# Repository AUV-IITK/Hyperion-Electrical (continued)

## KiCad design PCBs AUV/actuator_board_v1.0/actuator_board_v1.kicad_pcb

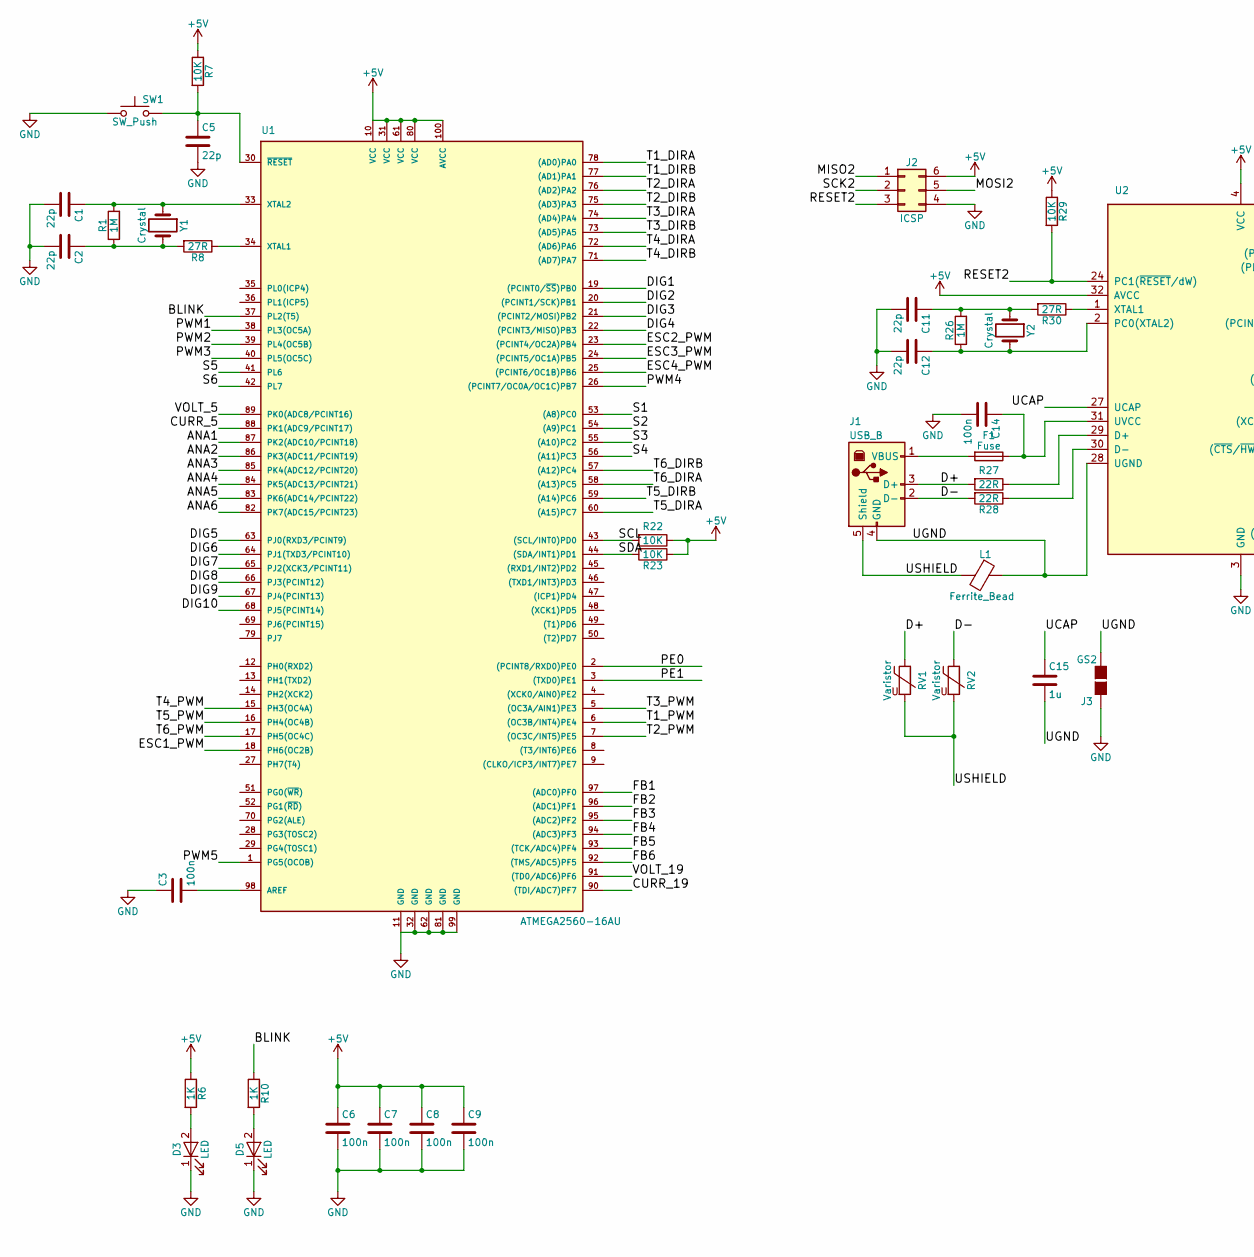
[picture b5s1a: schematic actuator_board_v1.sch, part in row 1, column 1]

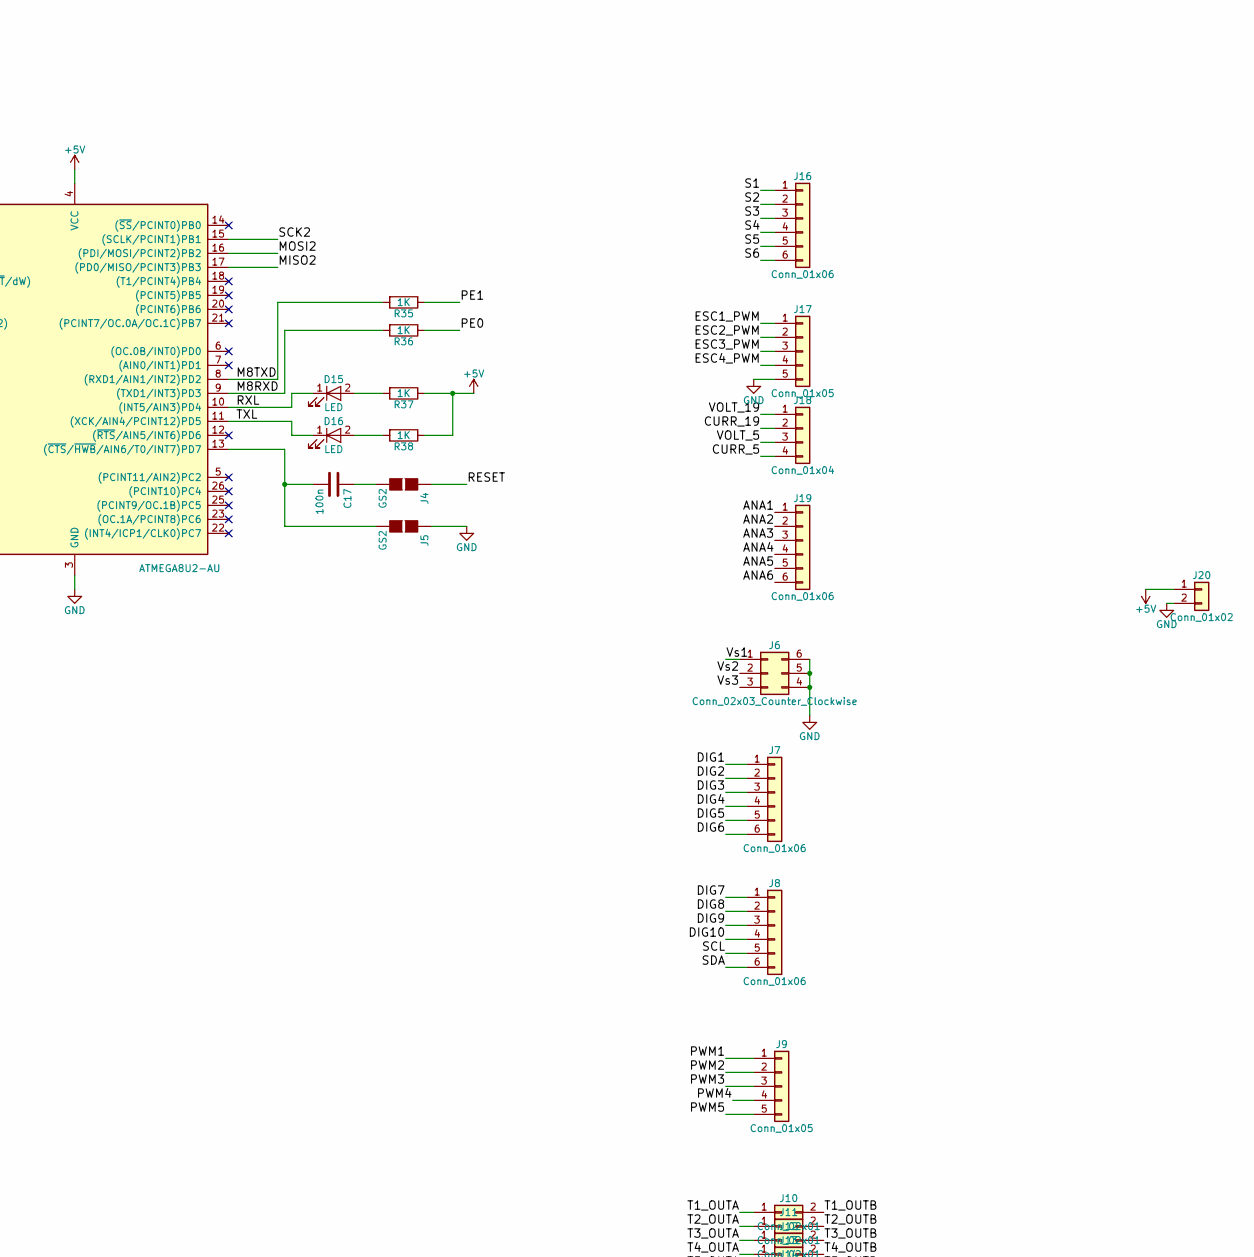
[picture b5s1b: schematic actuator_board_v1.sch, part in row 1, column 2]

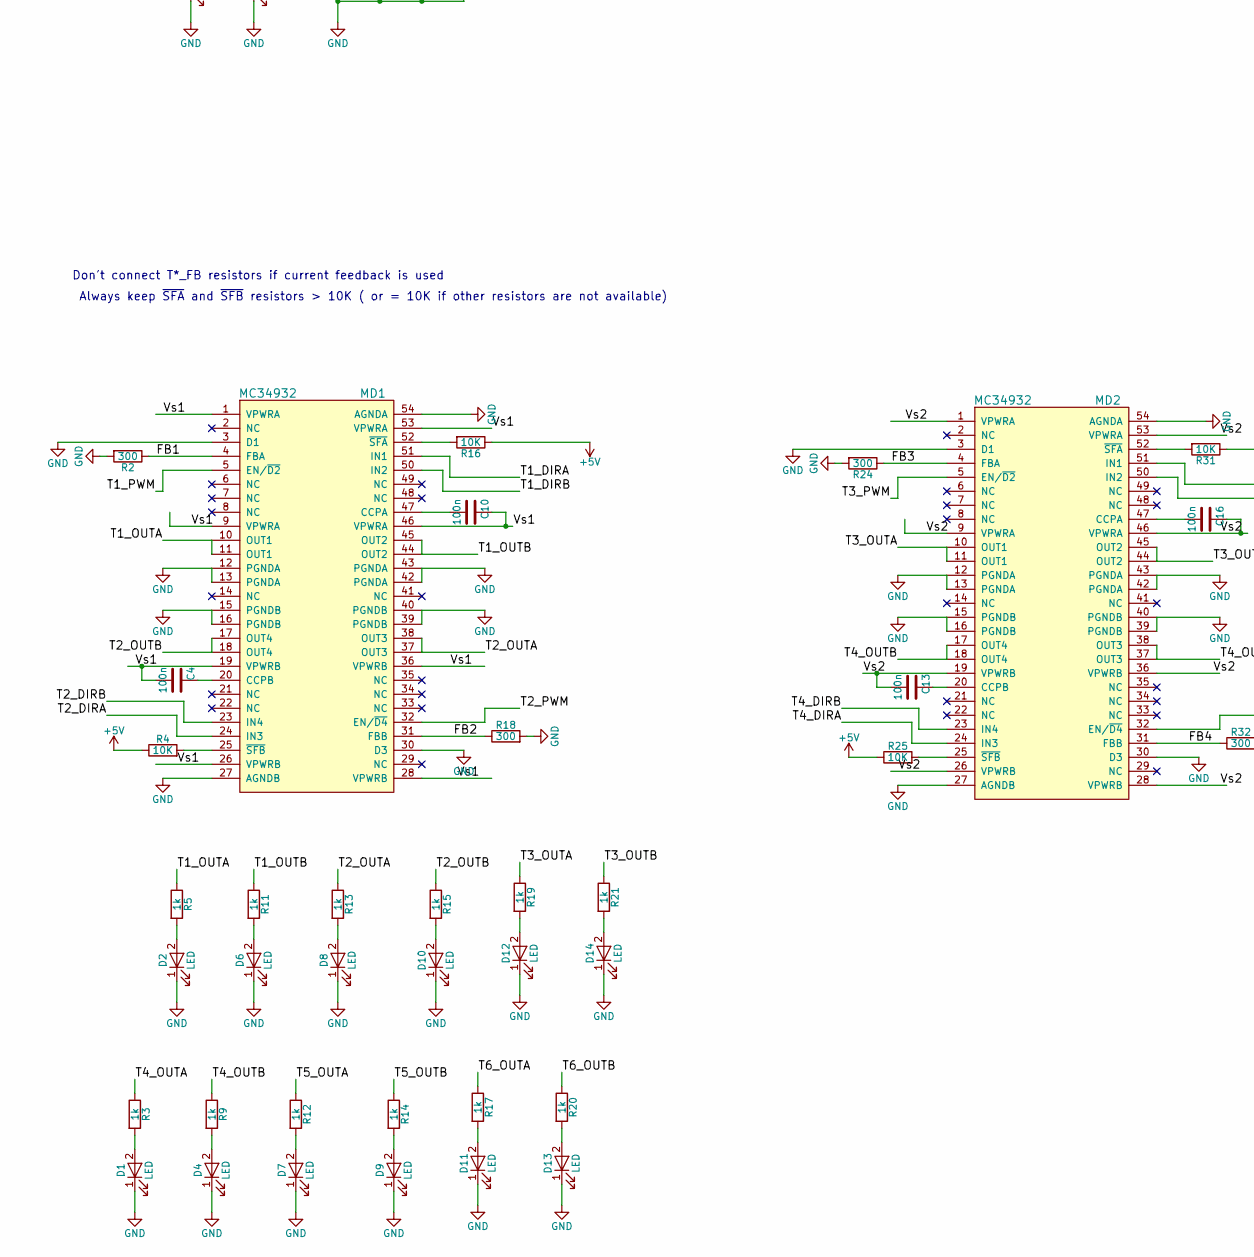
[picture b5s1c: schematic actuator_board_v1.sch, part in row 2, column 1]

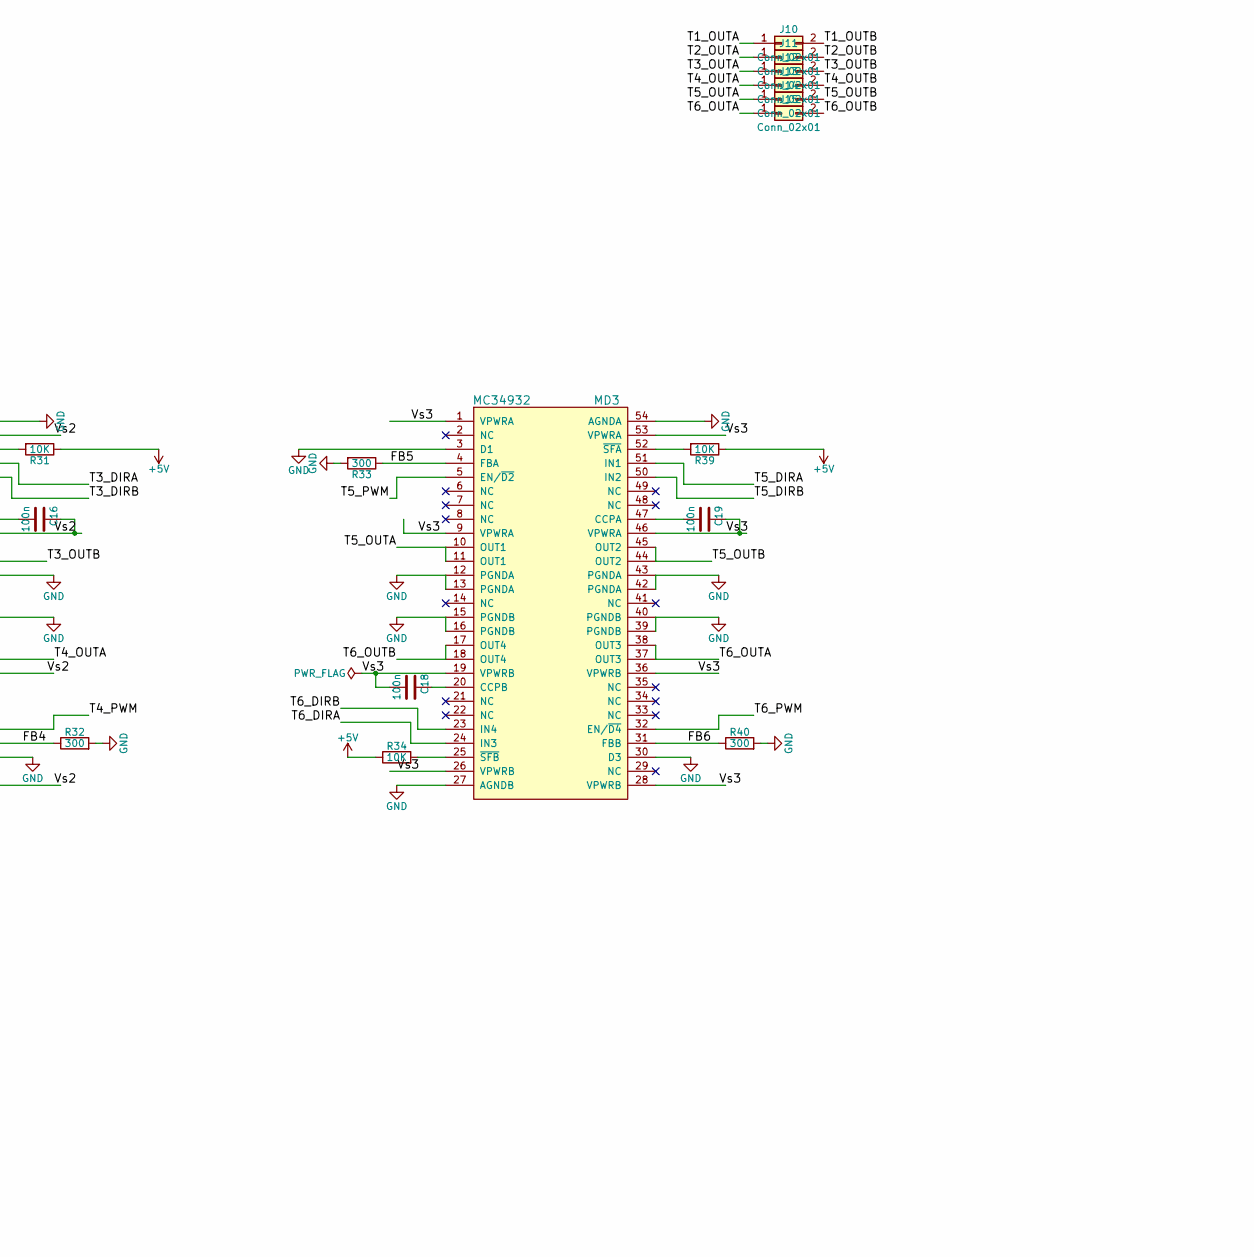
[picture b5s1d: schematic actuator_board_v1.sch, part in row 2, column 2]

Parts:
C1, C2, C5, C11, C12: 22p; C_1206
C3, C4, C6, C7, C8, C9, C10, C13, C14, C16, C17, C18, C19: 100n; C_1206
C15: 1u; C_1206
D1, D2, D3, D4, D5, D6, D7, D8, D9, D10, D11, D12, D13, D14, D15, D16: LED; LED_1206
F1: Fuse
J1: USB_B
J2: ICSP
J3, J4, J5: GS2
J6: Conn_02x03_Counter_Clockwise; Molex_MegaFit_2x03x5.70mm_Straight
J7, J8, J16, J19: Conn_01x06; Molex_PicoClasp_501331-0607_1x06_P1.0mm_Vertical
J9, J17: Conn_01x05; Molex_PicoClasp_501331-0507_1x05_P1.0mm_Vertical
J10, J11, J12, J13, J14, J15: Conn_02x01; Molex_MegaFit_2x01x5.70mm_Straight
J18: Conn_01x04; Molex_PicoClasp_501331-0407_1x04_P1.0mm_Vertical
J20: Conn_01x02; Molex_MegaFit_2x01x5.70mm_Straight
L1: Ferrite_Bead; 0603-NO
MD1, MD2, MD3: MC34932; SOIC-54(SOICW-EP-54)
R1, R26: 1M; R_1206
R2, R18, R24, R32, R33, R40: 300; R_1206
R3, R5, R9, R11, R12, R13, R14, R15, R17, R19, R20, R21: 1k; R_1206
R4, R7, R16, R22, R23, R25, R29, R31, R34, R39: 10K; R_1206
R6, R10, R35, R36, R37, R38: 1K; R_1206
R8, R30: 27R; R_1206
R27, R28: 22R; R_1206
RV1, RV2: Varistor; 0603-NO
SW1: SW_Push; SW_PUSH_6mm_h5mm
U1: ATMEGA2560-16AU; TQFP100
U2: ATMEGA8U2-AU; TQFP-32
Y1, Y2: Crystal; Crystal_SMD_0603-4pin_6.0x3.5mm

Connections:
+5V: C6.1, C7.1, C8.1, C9.1, J2.6, J20.1, R4.1, R6.1, R7.1, R16.1, R22.1, R23.1, R25.1, R29.1, R31.1, R34.1, R37.1, R38.1, R39.1, U1.10 (VCC), U1.31 (VCC), U1.61 (VCC), U1.80 (VCC), U1.100 (AVCC), U2.4 (VCC), U2.32 (AVCC)
/ANA1: J19.1, U1.87 (PK2(ADC10/PCINT18))
/ANA2: J19.2, U1.86 (PK3(ADC11/PCINT19))
/ANA3: J19.3, U1.85 (PK4(ADC12/PCINT20))
/ANA4: J19.4, U1.84 (PK5(ADC13/PCINT21))
/ANA5: J19.5, U1.83 (PK6(ADC14/PCINT22))
/ANA6: J19.6, U1.82 (PK7(ADC15/PCINT23))
/BLINK: R10.1, U1.37 (PL2(T5))
/CURR_5: J18.4, U1.88 (PK1(ADC9/PCINT17))
/CURR_19: J18.2, U1.90 ((TDI/ADC7)PF7)
/D+: J1.3 (D+), R27.2, RV1.1
/D-: J1.2 (D-), R28.2, RV2.1
/DIG1: J7.1, U1.19 ((PCINT0/~SS~)PB0)
/DIG2: J7.2, U1.20 ((PCINT1/SCK)PB1)
/DIG3: J7.3, U1.21 ((PCINT2/MOSI)PB2)
/DIG4: J7.4, U1.22 ((PCINT3/MISO)PB3)
/DIG5: J7.5, U1.63 (PJ0(RXD3/PCINT9))
/DIG6: J7.6, U1.64 (PJ1(TXD3/PCINT10))
/DIG7: J8.1, U1.65 (PJ2(XCK3/PCINT11))
/DIG8: J8.2, U1.66 (PJ3(PCINT12))
/DIG9: J8.3, U1.67 (PJ4(PCINT13))
/DIG10: J8.4, U1.68 (PJ5(PCINT14))
/ESC1_PWM: J17.1, U1.18 (PH6(OC2B))
/ESC2_PWM: J17.2, U1.23 ((PCINT4/OC2A)PB4)
/ESC3_PWM: J17.3, U1.24 ((PCINT5/OC1A)PB5)
/ESC4_PWM: J17.4, U1.25 ((PCINT6/OC1B)PB6)
/FB1: MD1.4 (FBA), R2.1, U1.97 ((ADC0)PF0)
/FB2: MD1.31 (FBB), R18.1, U1.96 ((ADC1)PF1)
/FB3: MD2.4 (FBA), R24.1, U1.95 ((ADC2)PF2)
/FB4: MD2.31 (FBB), R32.1, U1.94 ((ADC3)PF3)
/FB5: MD3.4 (FBA), R33.1, U1.93 ((TCK/ADC4)PF4)
/FB6: MD3.31 (FBB), R40.1, U1.92 ((TMS/ADC5)PF5)
/M8RXD: R36.2, U2.9 ((TXD1/INT3)PD3)
/M8TXD: R35.2, U2.8 ((RXD1/AIN1/INT2)PD2)
/MISO2: J2.1, U2.17 ((PD0/MISO/PCINT3)PB3)
/MOSI2: J2.5, U2.16 ((PDI/MOSI/PCINT2)PB2)
/PE0: R36.1, U1.2 ((PCINT8/RXD0)PE0)
/PE1: R35.1, U1.3 ((TXD0)PE1)
/PWM1: J9.1, U1.38 (PL3(OC5A))
/PWM2: J9.2, U1.39 (PL4(OC5B))
/PWM3: J9.3, U1.40 (PL5(OC5C))
/PWM4: J9.4, U1.26 ((PCINT7/OC0A/OC1C)PB7)
/PWM5: J9.5, U1.1 (PG5(OCOB))
/RESET: J4.1 (G1)
/RESET2: J2.3, R29.2, U2.24 (PC1(~RESET~/dW))
/RXL: D15.1 (K), U2.10 ((INT5/AIN3)PD4)
/S1: J16.1, U1.53 ((A8)PC0)
/S2: J16.2, U1.54 ((A9)PC1)
/S3: J16.3, U1.55 ((A10)PC2)
/S4: J16.4, U1.56 ((A11)PC3)
/S5: J16.5, U1.41 (PL6)
/S6: J16.6, U1.42 (PL7)
/SCK2: J2.2, U2.15 ((SCLK/PCINT1)PB1)
/SCL: J8.5, R22.2, U1.43 ((SCL/INT0)PD0)
/SDA: J8.6, R23.2, U1.44 ((SDA/INT1)PD1)
/T1_DIRA: MD1.51 (IN1), U1.78 ((AD0)PA0)
/T1_DIRB: MD1.50 (IN2), U1.77 ((AD1)PA1)
/T1_OUTA: J10.1, MD1.10 (OUT1), MD1.11 (OUT1), R5.1
/T1_OUTB: J10.2, MD1.44 (OUT2), MD1.45 (OUT2), R11.1
/T1_PWM: MD1.5 (EN/~D2~), U1.6 ((OC3B/INT4)PE4)
/T2_DIRA: MD1.24 (IN3), U1.76 ((AD2)PA2)
/T2_DIRB: MD1.23 (IN4), U1.75 ((AD3)PA3)
/T2_OUTA: J11.1, MD1.37 (OUT3), MD1.38 (OUT3), R13.1
/T2_OUTB: J11.2, MD1.17 (OUT4), MD1.18 (OUT4), R15.1
/T2_PWM: MD1.32 (EN/~D4~), U1.7 ((OC3C/INT5)PE5)
/T3_DIRA: MD2.51 (IN1), U1.74 ((AD4)PA4)
/T3_DIRB: MD2.50 (IN2), U1.73 ((AD5)PA5)
/T3_OUTA: J12.1, MD2.10 (OUT1), MD2.11 (OUT1), R19.1
/T3_OUTB: J12.2, MD2.44 (OUT2), MD2.45 (OUT2), R21.1
/T3_PWM: MD2.5 (EN/~D2~), U1.5 ((OC3A/AIN1)PE3)
/T4_DIRA: MD2.24 (IN3), U1.72 ((AD6)PA6)
/T4_DIRB: MD2.23 (IN4), U1.71 ((AD7)PA7)
/T4_OUTA: J13.1, MD2.37 (OUT3), MD2.38 (OUT3), R3.1
/T4_OUTB: J13.2, MD2.17 (OUT4), MD2.18 (OUT4), R9.1
/T4_PWM: MD2.32 (EN/~D4~), U1.15 (PH3(OC4A))
/T5_DIRA: MD3.51 (IN1), U1.60 ((A15)PC7)
/T5_DIRB: MD3.50 (IN2), U1.59 ((A14)PC6)
/T5_OUTA: J14.1, MD3.10 (OUT1), MD3.11 (OUT1), R12.1
/T5_OUTB: J14.2, MD3.44 (OUT2), MD3.45 (OUT2), R14.1
/T5_PWM: MD3.5 (EN/~D2~), U1.16 (PH4(OC4B))
/T6_DIRA: MD3.24 (IN3), U1.58 ((A13)PC5)
/T6_DIRB: MD3.23 (IN4), U1.57 ((A12)PC4)
/T6_OUTA: J15.1, MD3.37 (OUT3), MD3.38 (OUT3), R17.1
/T6_OUTB: J15.2, MD3.17 (OUT4), MD3.18 (OUT4), R20.1
/T6_PWM: MD3.32 (EN/~D4~), U1.17 (PH5(OC4C))
/TXL: D16.1 (K), U2.11 ((XCK/AIN4/PCINT12)PD5)
/UCAP: C15.1, U2.27 (UCAP)
/UGND: C15.2, J1.4 (GND), J3.2 (G2), L1.1, U2.28 (UGND)
/USHIELD: J1.5 (Shield), L1.2, RV1.2, RV2.2
/VOLT_5: J18.3, U1.89 (PK0(ADC8/PCINT16))
/VOLT_19: J18.1, U1.91 ((TD0/ADC6)PF6)
/Vs1: C4.2, C10.1, J6.1, MD1.1 (VPWRA), MD1.9 (VPWRA), MD1.19 (VPWRB), MD1.26 (VPWRB), MD1.28 (VPWRB), MD1.36 (VPWRB), MD1.46 (VPWRA), MD1.53 (VPWRA)
/Vs2: C13.2, C16.1, J6.2, MD2.1 (VPWRA), MD2.9 (VPWRA), MD2.19 (VPWRB), MD2.26 (VPWRB), MD2.28 (VPWRB), MD2.36 (VPWRB), MD2.46 (VPWRA), MD2.53 (VPWRA)
/Vs3: C18.2, C19.1, J6.3, MD3.1 (VPWRA), MD3.9 (VPWRA), MD3.19 (VPWRB), MD3.26 (VPWRB), MD3.28 (VPWRB), MD3.36 (VPWRB), MD3.46 (VPWRA), MD3.53 (VPWRA)
GND: C1.2, C2.2, C3.1, C5.2, C6.2, C7.2, C8.2, C9.2, C11.2, C12.2, C14.2, D1.1 (K), D2.1 (K), D3.1 (K), D4.1 (K), D5.1 (K), D6.1 (K), D7.1 (K), D8.1 (K), D9.1 (K), D10.1 (K), D11.1 (K), D12.1 (K), D13.1 (K), D14.1 (K), J2.4, J3.1 (G1), J5.1 (G1), J6.4, J6.5, J6.6, J17.5, J20.2, MD1.3 (D1), MD1.12 (PGNDA), MD1.13 (PGNDA), MD1.15 (PGNDB), MD1.16 (PGNDB), MD1.27 (AGNDB), MD1.30 (D3), MD1.39 (PGNDB), MD1.40 (PGNDB), MD1.42 (PGNDA), MD1.43 (PGNDA), MD1.54 (AGNDA), MD2.3 (D1), MD2.12 (PGNDA), MD2.13 (PGNDA), MD2.15 (PGNDB), MD2.16 (PGNDB), MD2.27 (AGNDB), MD2.30 (D3), MD2.39 (PGNDB), MD2.40 (PGNDB), MD2.42 (PGNDA), MD2.43 (PGNDA), MD2.54 (AGNDA), MD3.3 (D1), MD3.12 (PGNDA), MD3.13 (PGNDA), MD3.15 (PGNDB), MD3.16 (PGNDB), MD3.27 (AGNDB), MD3.30 (D3), MD3.39 (PGNDB), MD3.40 (PGNDB), MD3.42 (PGNDA), MD3.43 (PGNDA), MD3.54 (AGNDA), R2.2, R18.2, R24.2, R32.2, R33.2, R40.2, SW1.1, U1.11 (GND), U1.32 (GND), U1.62 (GND), U1.81 (GND), U1.99 (GND), U2.3 (GND)
unnamed: C1.1, R1.2, U1.33 (XTAL2), Y1.1
unnamed: C2.1, R1.1, R8.2, Y1.2
unnamed: C3.2, U1.98 (AREF)
unnamed: C4.1, MD1.20 (CCPB)
unnamed: C5.1, R7.2, SW1.2, U1.30 (~RESET)
unnamed: C10.2, MD1.47 (CCPA)
unnamed: C11.1, R26.2, R30.2, Y2.1
unnamed: C12.1, R26.1, U2.2 (PC0(XTAL2)), Y2.2
unnamed: C13.1, MD2.20 (CCPB)
unnamed: C14.1, F1.1, U2.31 (UVCC)
unnamed: C16.2, MD2.47 (CCPA)
unnamed: C17.1, J4.2 (G2)
unnamed: C17.2, J5.2 (G2), U2.13 ((~CTS~/~HWB~/AIN6/T0/INT7)PD7)
unnamed: C18.1, MD3.20 (CCPB)
unnamed: C19.2, MD3.47 (CCPA)
unnamed: D1.2 (A), R3.2
unnamed: D2.2 (A), R5.2
unnamed: D3.2 (A), R6.2
unnamed: D4.2 (A), R9.2
unnamed: D5.2 (A), R10.2
unnamed: D6.2 (A), R11.2
unnamed: D7.2 (A), R12.2
unnamed: D8.2 (A), R13.2
unnamed: D9.2 (A), R14.2
unnamed: D10.2 (A), R15.2
unnamed: D11.2 (A), R17.2
unnamed: D12.2 (A), R19.2
unnamed: D13.2 (A), R20.2
unnamed: D14.2 (A), R21.2
unnamed: D15.2 (A), R37.2
unnamed: D16.2 (A), R38.2
unnamed: F1.2, J1.1 (VBUS)
unnamed: MD1.25 (~SFB~), R4.2
unnamed: MD1.52 (~SFA~), R16.2
unnamed: MD2.25 (~SFB~), R25.2
unnamed: MD2.52 (~SFA~), R31.2
unnamed: MD3.25 (~SFB~), R34.2
unnamed: MD3.52 (~SFA~), R39.2
unnamed: R8.1, U1.34 (XTAL1)
unnamed: R27.1, U2.29 (D+)
unnamed: R28.1, U2.30 (D-)
unnamed: R30.1, U2.1 (XTAL1)

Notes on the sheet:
Don't connect T*_FB resistors if current feedback is used
Always keep ~SFA~ and ~SFB~ resistors > 10K ( or = 10K if other resistors are not available)

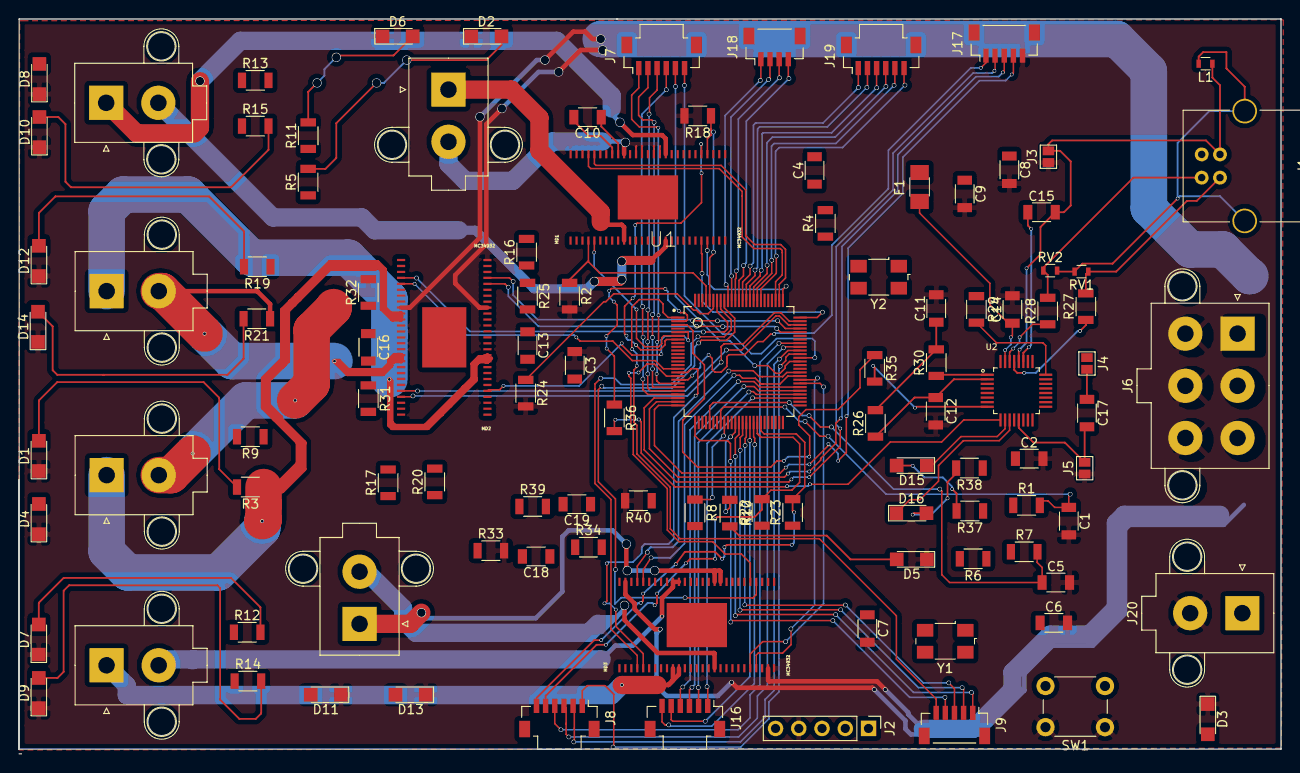
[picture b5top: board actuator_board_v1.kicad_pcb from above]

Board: 2 copper layers, 137.9 x 80.3 mm, 107 parts (0 on the bottom side), 136 nets.

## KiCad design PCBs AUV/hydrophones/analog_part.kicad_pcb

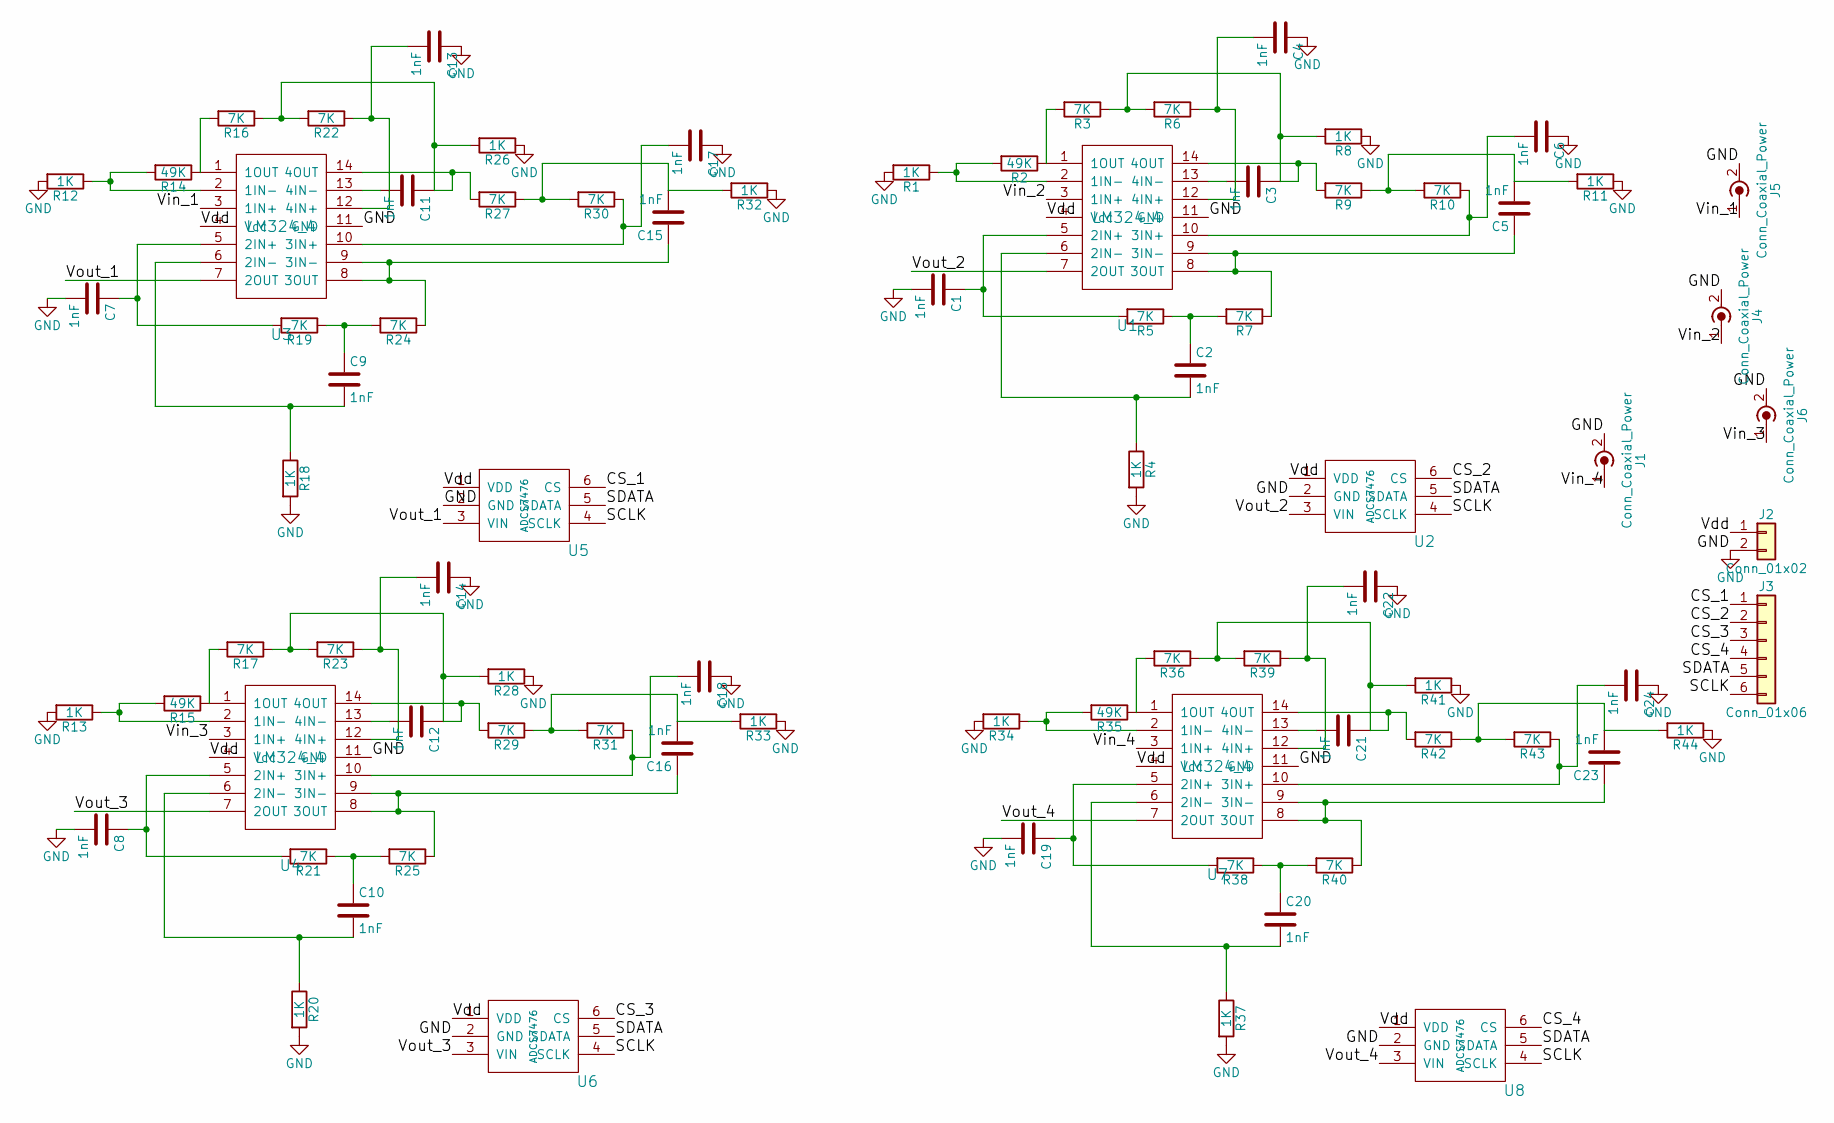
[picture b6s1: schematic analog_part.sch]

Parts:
C1, C2, C3, C4, C5, C6, C7, C8, C9, C10, C11, C12, C13, C14, C15, C16, C17, C18, C19, C20, C21, C22, C23, C24: 1nF; C_1206_HandSoldering
J1, J4, J5, J6: Conn_Coaxial_Power; bnc-ci
J2: Conn_01x02; Pin_Header_Angled_1x02_Pitch2.54mm
J3: Conn_01x06; Pin_Header_Angled_1x06_Pitch2.54mm
R1, R4, R8, R11, R12, R13, R18, R20, R26, R28, R32, R33, R34, R37, R41, R44: 1K; R_1206_HandSoldering
R2, R14, R15, R35: 49K; R_1206_HandSoldering
R3, R5, R6, R7, R9, R10, R16, R17, R19, R21, R22, R23, R24, R25, R27, R29, R30, R31, R36, R38, R39, R40, R42, R43: 7K; R_1206_HandSoldering
U1, U3, U4, U7: LM324_4; TSSOP-14_4.4x5mm_Pitch0.65mm
U2, U5, U6, U8: ADCS7476; SOT-23-6_Handsoldering

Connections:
/CS_1: J3.1, U5.6 (CS)
/CS_2: J3.2, U2.6 (CS)
/CS_3: J3.3, U6.6 (CS)
/CS_4: J3.4, U8.6 (CS)
/SCLK: J3.6, U2.4 (SCLK), U5.4 (SCLK), U6.4 (SCLK), U8.4 (SCLK)
/SDATA: J3.5, U2.5 (SDATA), U5.5 (SDATA), U6.5 (SDATA), U8.5 (SDATA)
/Vdd: J2.1, U1.4 (Vcc), U2.1 (VDD), U3.4 (Vcc), U4.4 (Vcc), U5.1 (VDD), U6.1 (VDD), U7.4 (Vcc), U8.1 (VDD)
/Vin_1: J5.1 (In), U3.3 (1IN+)
/Vin_2: J4.1 (In), U1.3 (1IN+)
/Vin_3: J6.1 (In), U4.3 (1IN+)
/Vin_4: J1.1 (In), U7.3 (1IN+)
/Vout_1: U3.7 (2OUT), U5.3 (VIN)
/Vout_2: U1.7 (2OUT), U2.3 (VIN)
/Vout_3: U4.7 (2OUT), U6.3 (VIN)
/Vout_4: U7.7 (2OUT), U8.3 (VIN)
GND: C1.2, C4.1, C6.1, C7.2, C8.2, C13.1, C14.1, C17.1, C18.1, C19.2, C22.1, C24.1, J1.2 (Ext), J2.2, J4.2 (Ext), J5.2 (Ext), J6.2 (Ext), R1.2, R4.2, R8.1, R11.1, R12.2, R13.2, R18.2, R20.2, R26.1, R28.1, R32.1, R33.1, R34.2, R37.2, R41.1, R44.1, U1.11 (GND), U2.2 (GND), U3.11 (GND), U4.11 (GND), U5.2 (GND), U6.2 (GND), U7.11 (GND), U8.2 (GND)
unnamed: C1.1, R5.2, U1.5 (2IN+)
unnamed: C2.1, R5.1, R7.2
unnamed: C2.2, R4.1, U1.6 (2IN-)
unnamed: C3.1, R3.1, R6.2, R8.2, R9.2, U1.14 (4OUT)
unnamed: C3.2, U1.13 (4IN-)
unnamed: C4.2, R6.1, U1.12 (4IN+)
unnamed: C5.1, R7.1, U1.8 (3OUT), U1.9 (3IN-)
unnamed: C5.2, R9.1, R10.2, R11.2
unnamed: C6.2, R10.1, U1.10 (3IN+)
unnamed: C7.1, R19.2, U3.5 (2IN+)
unnamed: C8.1, R21.2, U4.5 (2IN+)
unnamed: C9.1, R19.1, R24.2
unnamed: C9.2, R18.1, U3.6 (2IN-)
unnamed: C10.1, R21.1, R25.2
unnamed: C10.2, R20.1, U4.6 (2IN-)
unnamed: C11.1, R16.1, R22.2, R26.2, R27.2, U3.14 (4OUT)
unnamed: C11.2, U3.13 (4IN-)
unnamed: C12.1, R17.1, R23.2, R28.2, R29.2, U4.14 (4OUT)
unnamed: C12.2, U4.13 (4IN-)
unnamed: C13.2, R22.1, U3.12 (4IN+)
unnamed: C14.2, R23.1, U4.12 (4IN+)
unnamed: C15.1, R24.1, U3.8 (3OUT), U3.9 (3IN-)
unnamed: C15.2, R27.1, R30.2, R32.2
unnamed: C16.1, R25.1, U4.8 (3OUT), U4.9 (3IN-)
unnamed: C16.2, R29.1, R31.2, R33.2
unnamed: C17.2, R30.1, U3.10 (3IN+)
unnamed: C18.2, R31.1, U4.10 (3IN+)
unnamed: C19.1, R38.2, U7.5 (2IN+)
unnamed: C20.1, R38.1, R40.2
unnamed: C20.2, R37.1, U7.6 (2IN-)
unnamed: C21.1, R36.1, R39.2, R41.2, R42.2, U7.14 (4OUT)
unnamed: C21.2, U7.13 (4IN-)
unnamed: C22.2, R39.1, U7.12 (4IN+)
unnamed: C23.1, R40.1, U7.8 (3OUT), U7.9 (3IN-)
unnamed: C23.2, R42.1, R43.2, R44.2
unnamed: C24.2, R43.1, U7.10 (3IN+)
unnamed: R1.1, R2.2, U1.2 (1IN-)
unnamed: R2.1, R3.2, U1.1 (1OUT)
unnamed: R12.1, R14.2, U3.2 (1IN-)
unnamed: R13.1, R15.2, U4.2 (1IN-)
unnamed: R14.1, R16.2, U3.1 (1OUT)
unnamed: R15.1, R17.2, U4.1 (1OUT)
unnamed: R34.1, R35.2, U7.2 (1IN-)
unnamed: R35.1, R36.2, U7.1 (1OUT)

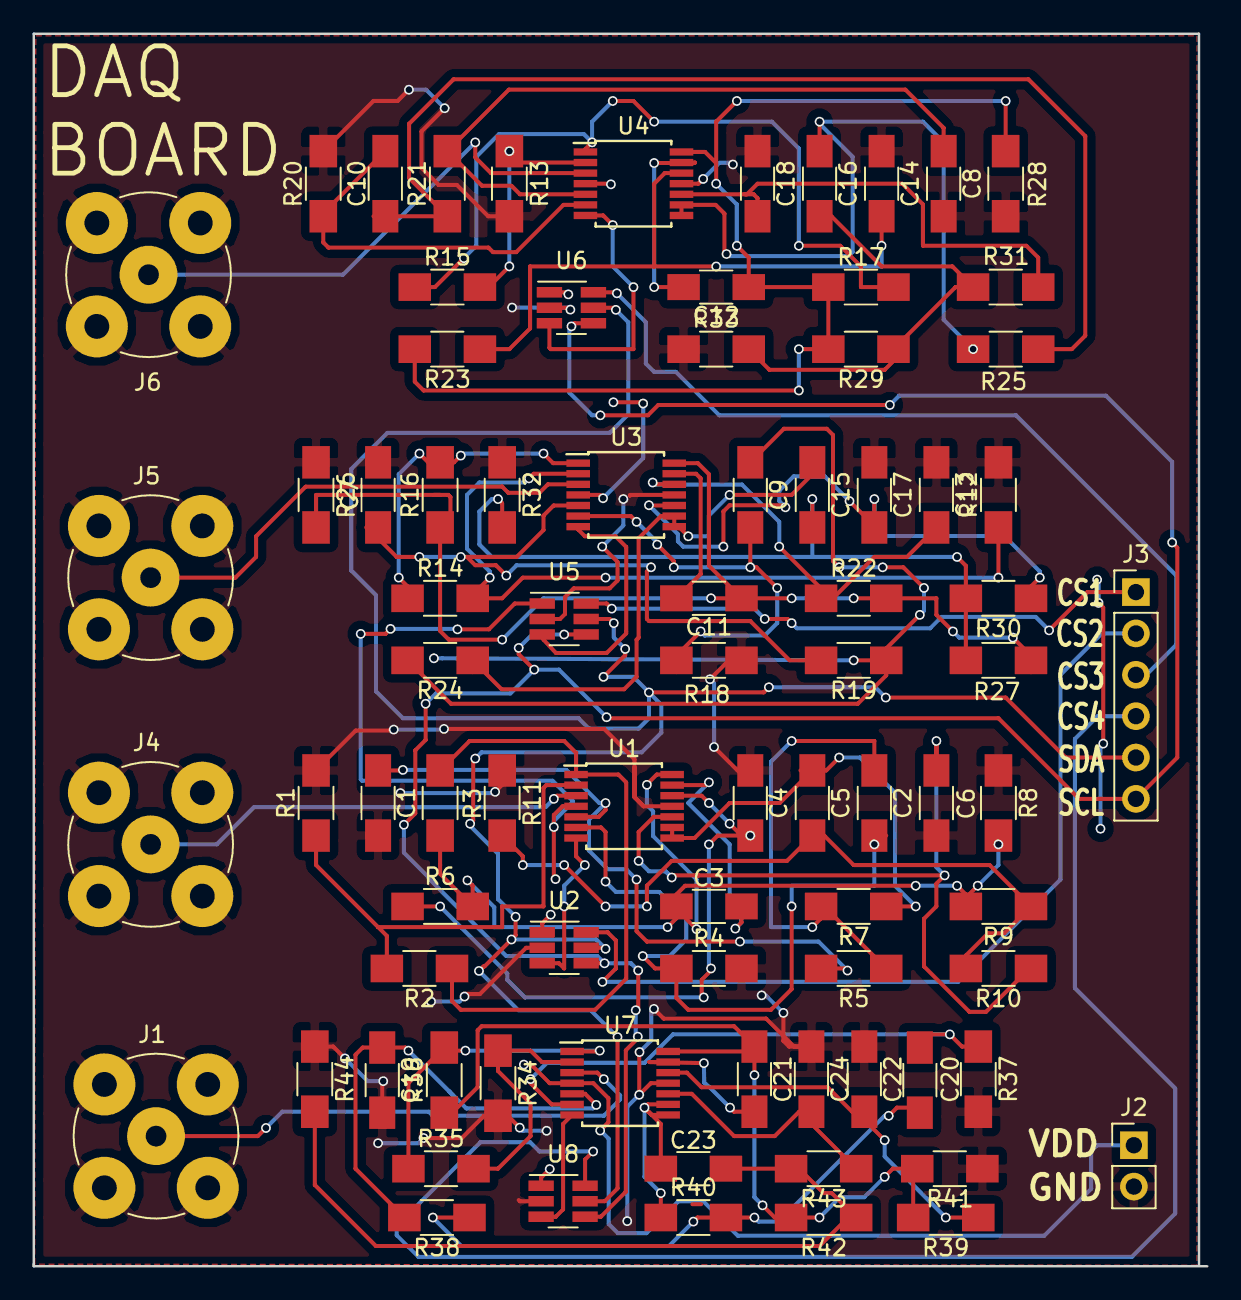
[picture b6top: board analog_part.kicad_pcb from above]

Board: 2 copper layers, 72.1 x 75.7 mm, 82 parts (0 on the bottom side), 60 nets.

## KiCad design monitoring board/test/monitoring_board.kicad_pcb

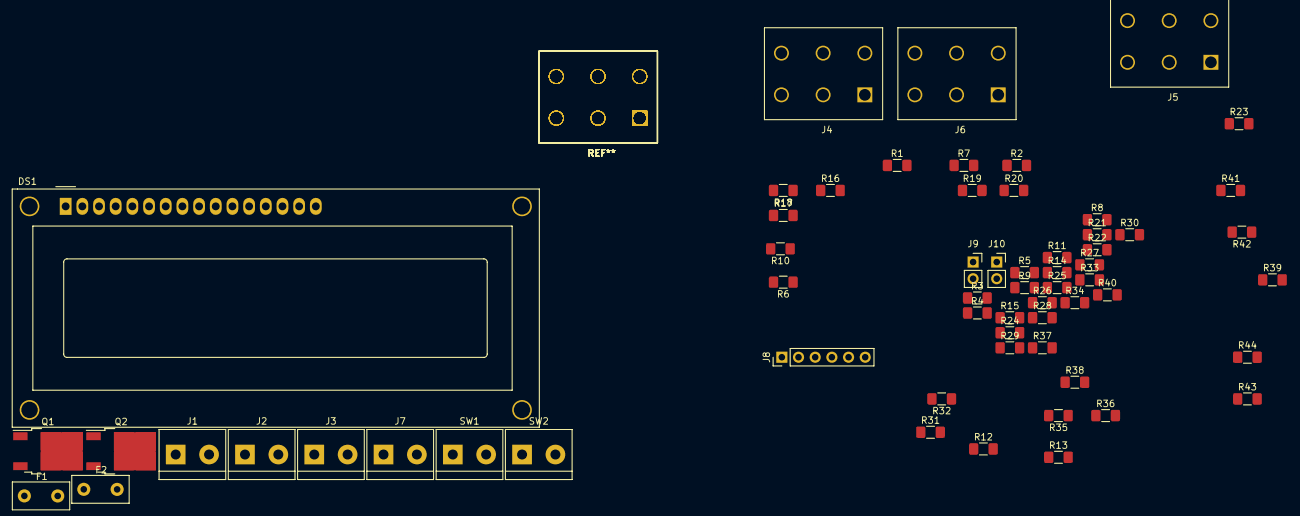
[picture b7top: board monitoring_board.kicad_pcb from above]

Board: 2 copper layers, 61 parts (0 on the bottom side), 44 nets, no tracks yet.

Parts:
DS1: WC1602A
F1: 30A Polyfuse; Fuse_TE5_Littlefuse-395Series
F2: 4A Polyfuse; Fuse_TE5_Littlefuse-395Series
J1, J2, J3, J7: Conn_01x02; TerminalBlock_bornier-2_P5.08mm
J4, J5, J6: Conn_02x03_Row_Letter_Last; Molex_mlx32_straight_header_6.35mm
J8: Conn_01x06_Male; PinHeader_1x06_P2.54mm_Vertical
J9, J10: Conn_01x02_Female; PinSocket_1x02_P2.54mm_Vertical
Q1, Q2: Q_PMOS_GDS; TO-252-2
R1, R2, R3, R4, R16, R18, R20, R22, R24, R26, R30, R32, R34, R36, R38, R42: 1K; R_1206_3216Metric_Pad1.42x1.75mm_HandSolder
R5, R6, R7, R8, R9, R10, R11, R12, R13, R14: 50m; R_1206_3216Metric_Pad1.42x1.75mm_HandSolder
R15, R17, R19, R21, R23, R25, R29, R31, R33, R35, R37, R39, R40, R41, R43, R44: 24K; R_1206_3216Metric_Pad1.42x1.75mm_HandSolder
R27: R; R_1206_3216Metric_Pad1.42x1.75mm_HandSolder
R28: 220; R_1206_3216Metric_Pad1.42x1.75mm_HandSolder
SW1, SW2: SW_DIP_x01; TerminalBlock_bornier-2_P5.08mm

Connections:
+5V: DS1.2, J3.1, R28.1
/23: DS1.11, J8.3
/24: DS1.12, J8.4
/25: DS1.13, J8.5
/26: DS1.14, J8.6
/27: DS1.6, J8.1
/28: DS1.4, J8.2
/A0: R19.1, R20.2
/A1: R15.1, R16.2
/A2: R23.1, R24.2
/A3: R29.1, R30.2
/A4: R37.1, R38.2
/A5: R17.1, R18.2
/A6: R21.1, R22.2
/A7: R31.1, R32.2
/A8: R35.1, R36.2
/A9: R25.1, R26.2
/A10: R33.1, R34.2
/A11: R41.1, R42.2
/SOV: R14.1, R41.2
/VBATT1: Q1.2, R39.2, SW1.2
/VBATT2: Q2.2, R43.2, SW2.2
/VESC1: R6.1, R15.2
/VESC2: R7.1, R23.2
/VESC3: R8.1, R29.2
/VESC4: R9.1, R37.2
/VESC5: R10.1, R17.2
/VESC6: R11.1, R21.2
/VESC7: R12.1, R31.2
/VESC8: R13.1, R35.2
/VIN1: F1.1, R6.2, R7.2, R8.2, R9.2, R10.2, R11.2, R12.2, R13.2, R14.2, R19.2
/VIN2: F2.1, R5.2, R25.2
/VNUC: J7.1, R5.1, R33.2
GND: DS1.1, DS1.5, DS1.16, J1.2, J2.2, J3.2, J7.2, J9.2, J10.2, R1.1, R2.1, R16.1, R18.1, R20.1, R22.1, R24.1, R26.1, R27.1, R30.1, R32.1, R34.1, R36.1, R38.1, R40.1, R42.1, R44.1
unnamed: DS1.3, R27.2
unnamed: DS1.15, R28.2
unnamed: F1.2, Q1.3, R3.2
unnamed: F2.2, Q2.3, R4.2
unnamed: J1.1, SW1.1
unnamed: J2.1, SW2.1
unnamed: J9.1, R39.1, R40.2
unnamed: J10.1, R43.1, R44.2
unnamed: Q1.1, R1.2, R3.1
unnamed: Q2.1, R2.2, R4.1
